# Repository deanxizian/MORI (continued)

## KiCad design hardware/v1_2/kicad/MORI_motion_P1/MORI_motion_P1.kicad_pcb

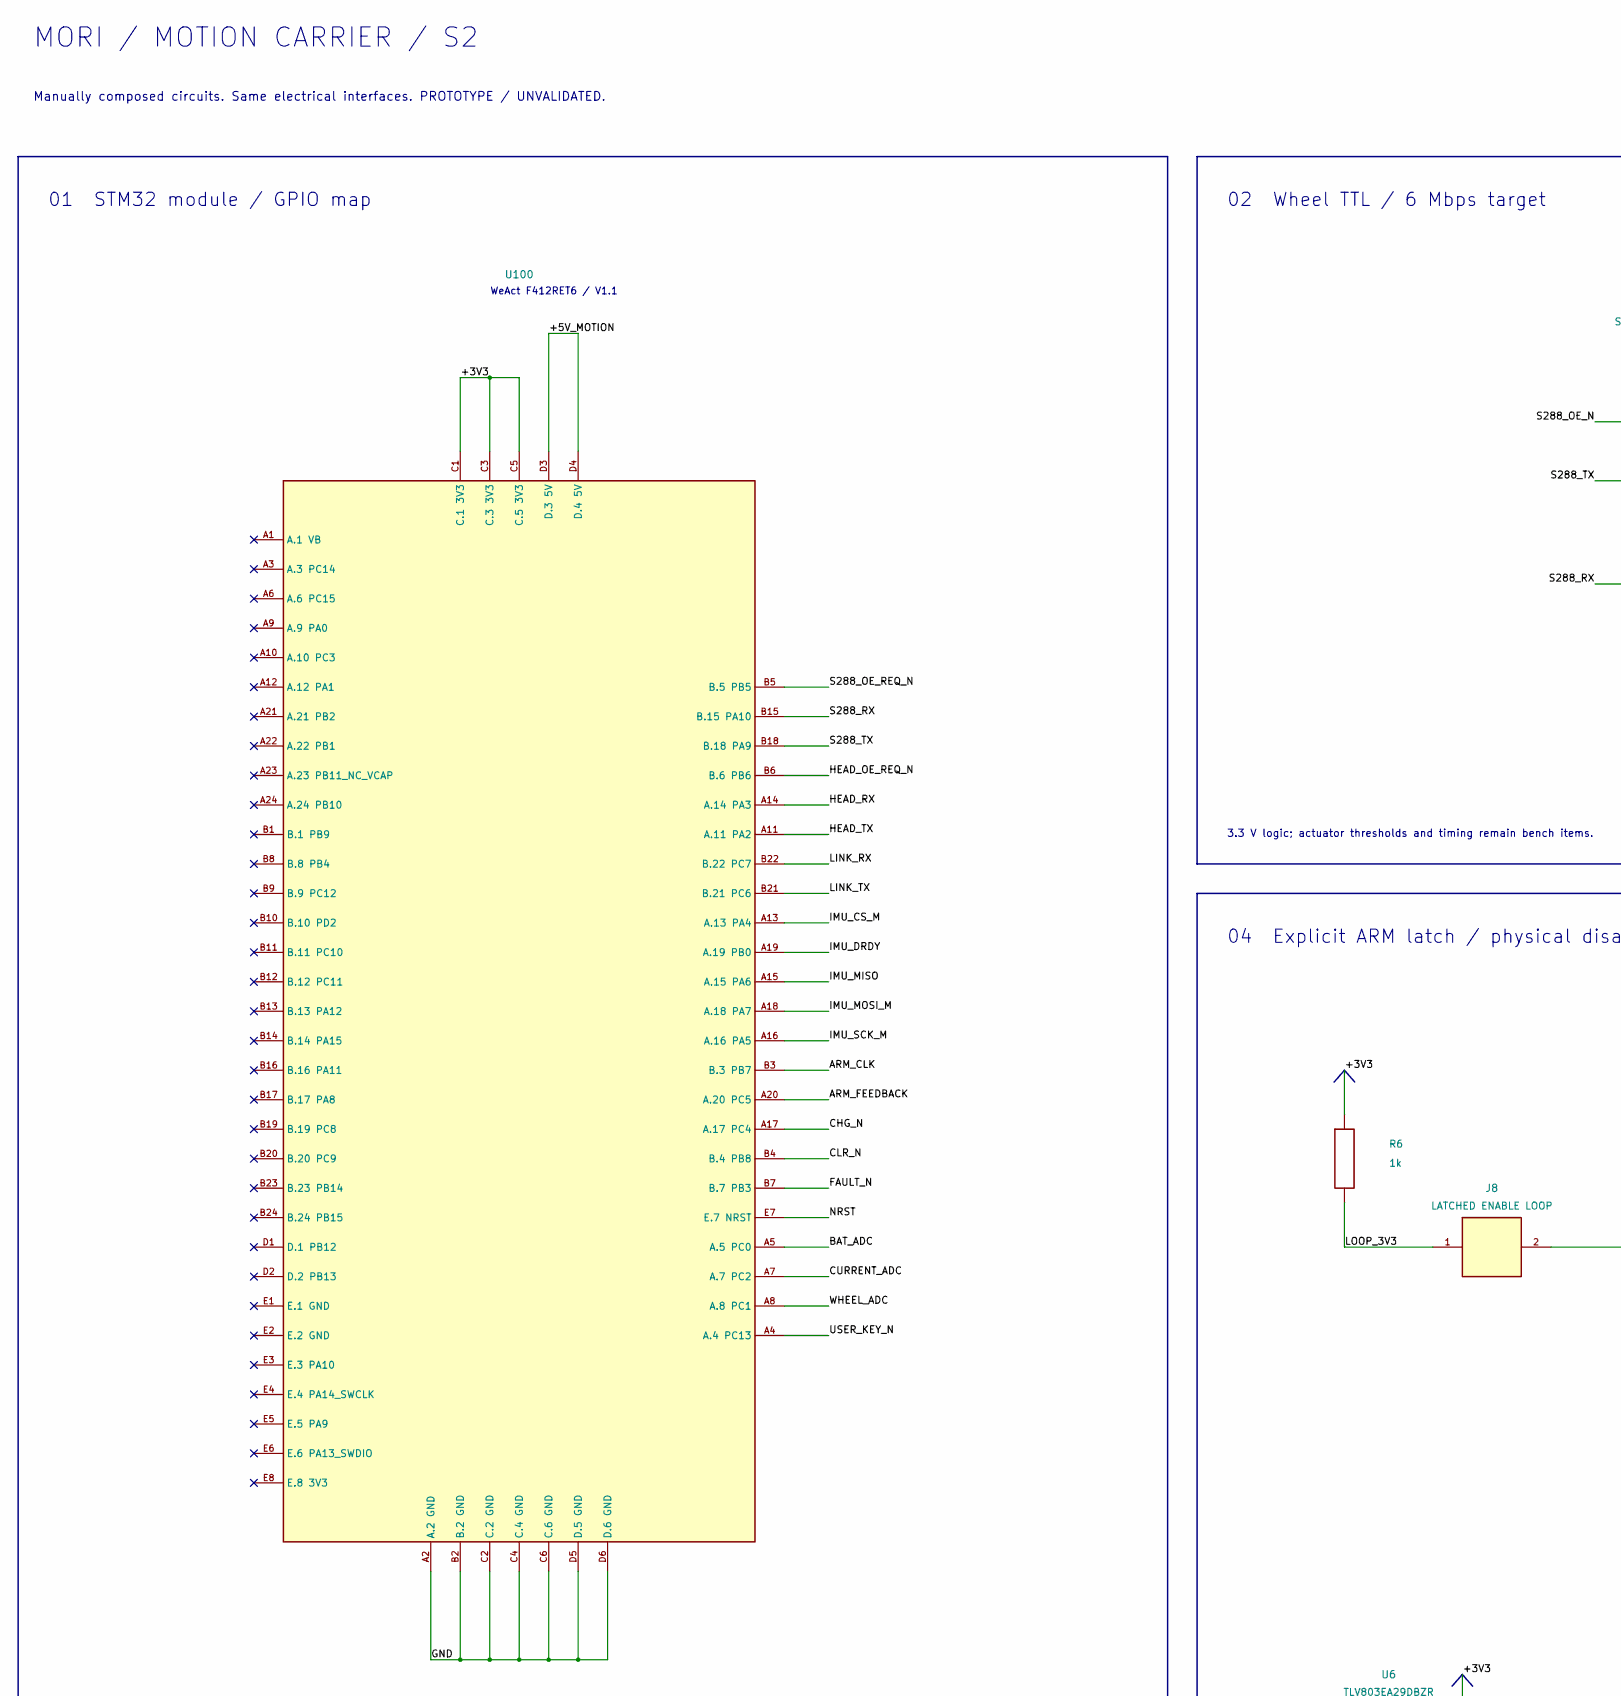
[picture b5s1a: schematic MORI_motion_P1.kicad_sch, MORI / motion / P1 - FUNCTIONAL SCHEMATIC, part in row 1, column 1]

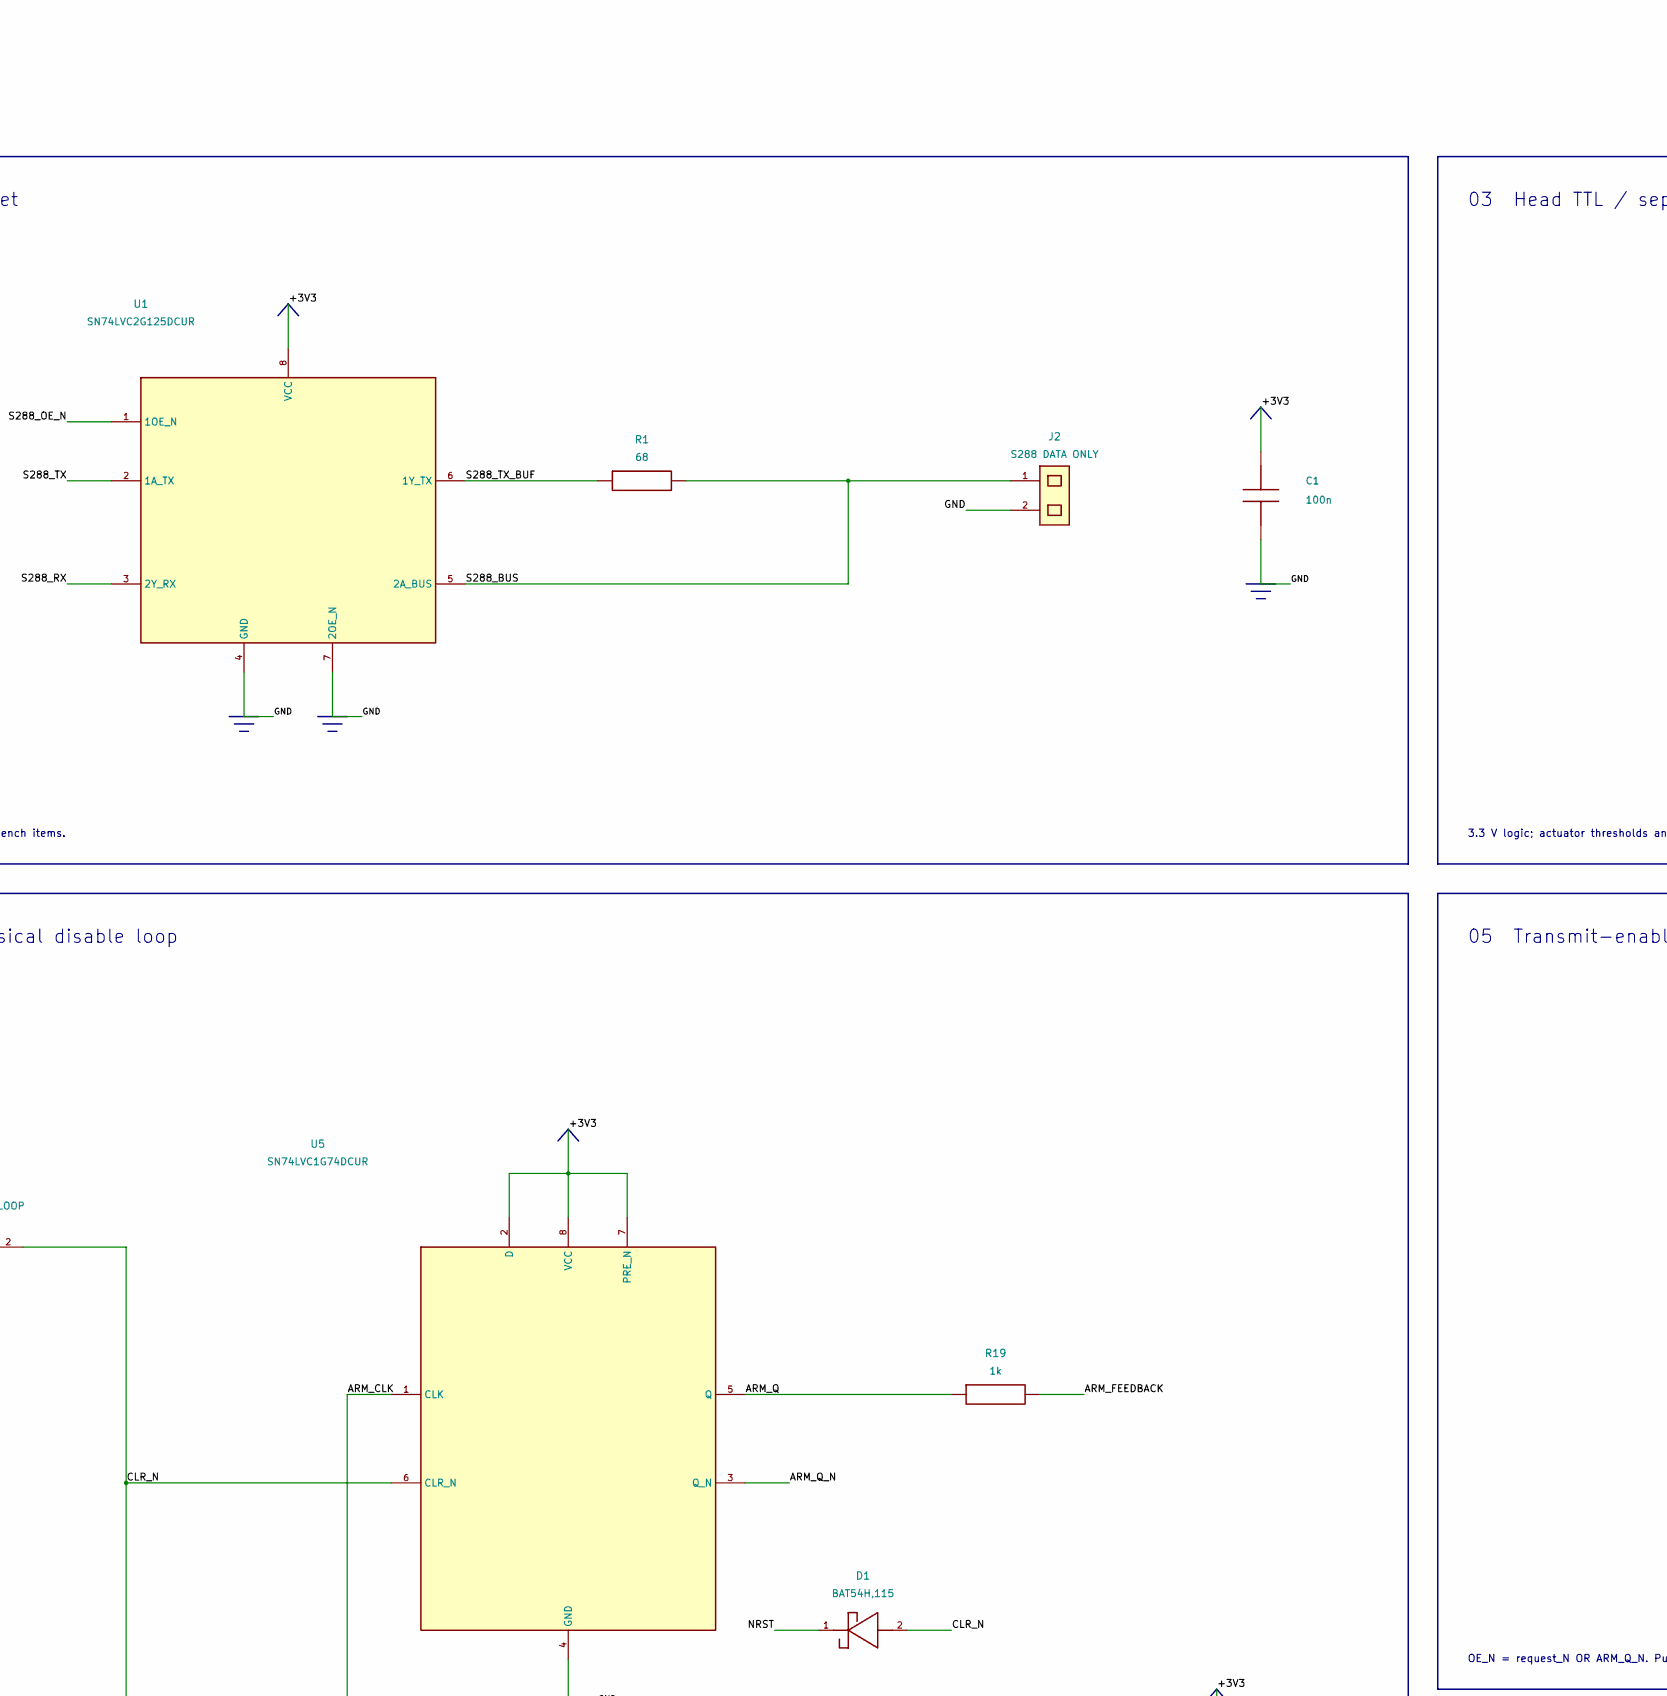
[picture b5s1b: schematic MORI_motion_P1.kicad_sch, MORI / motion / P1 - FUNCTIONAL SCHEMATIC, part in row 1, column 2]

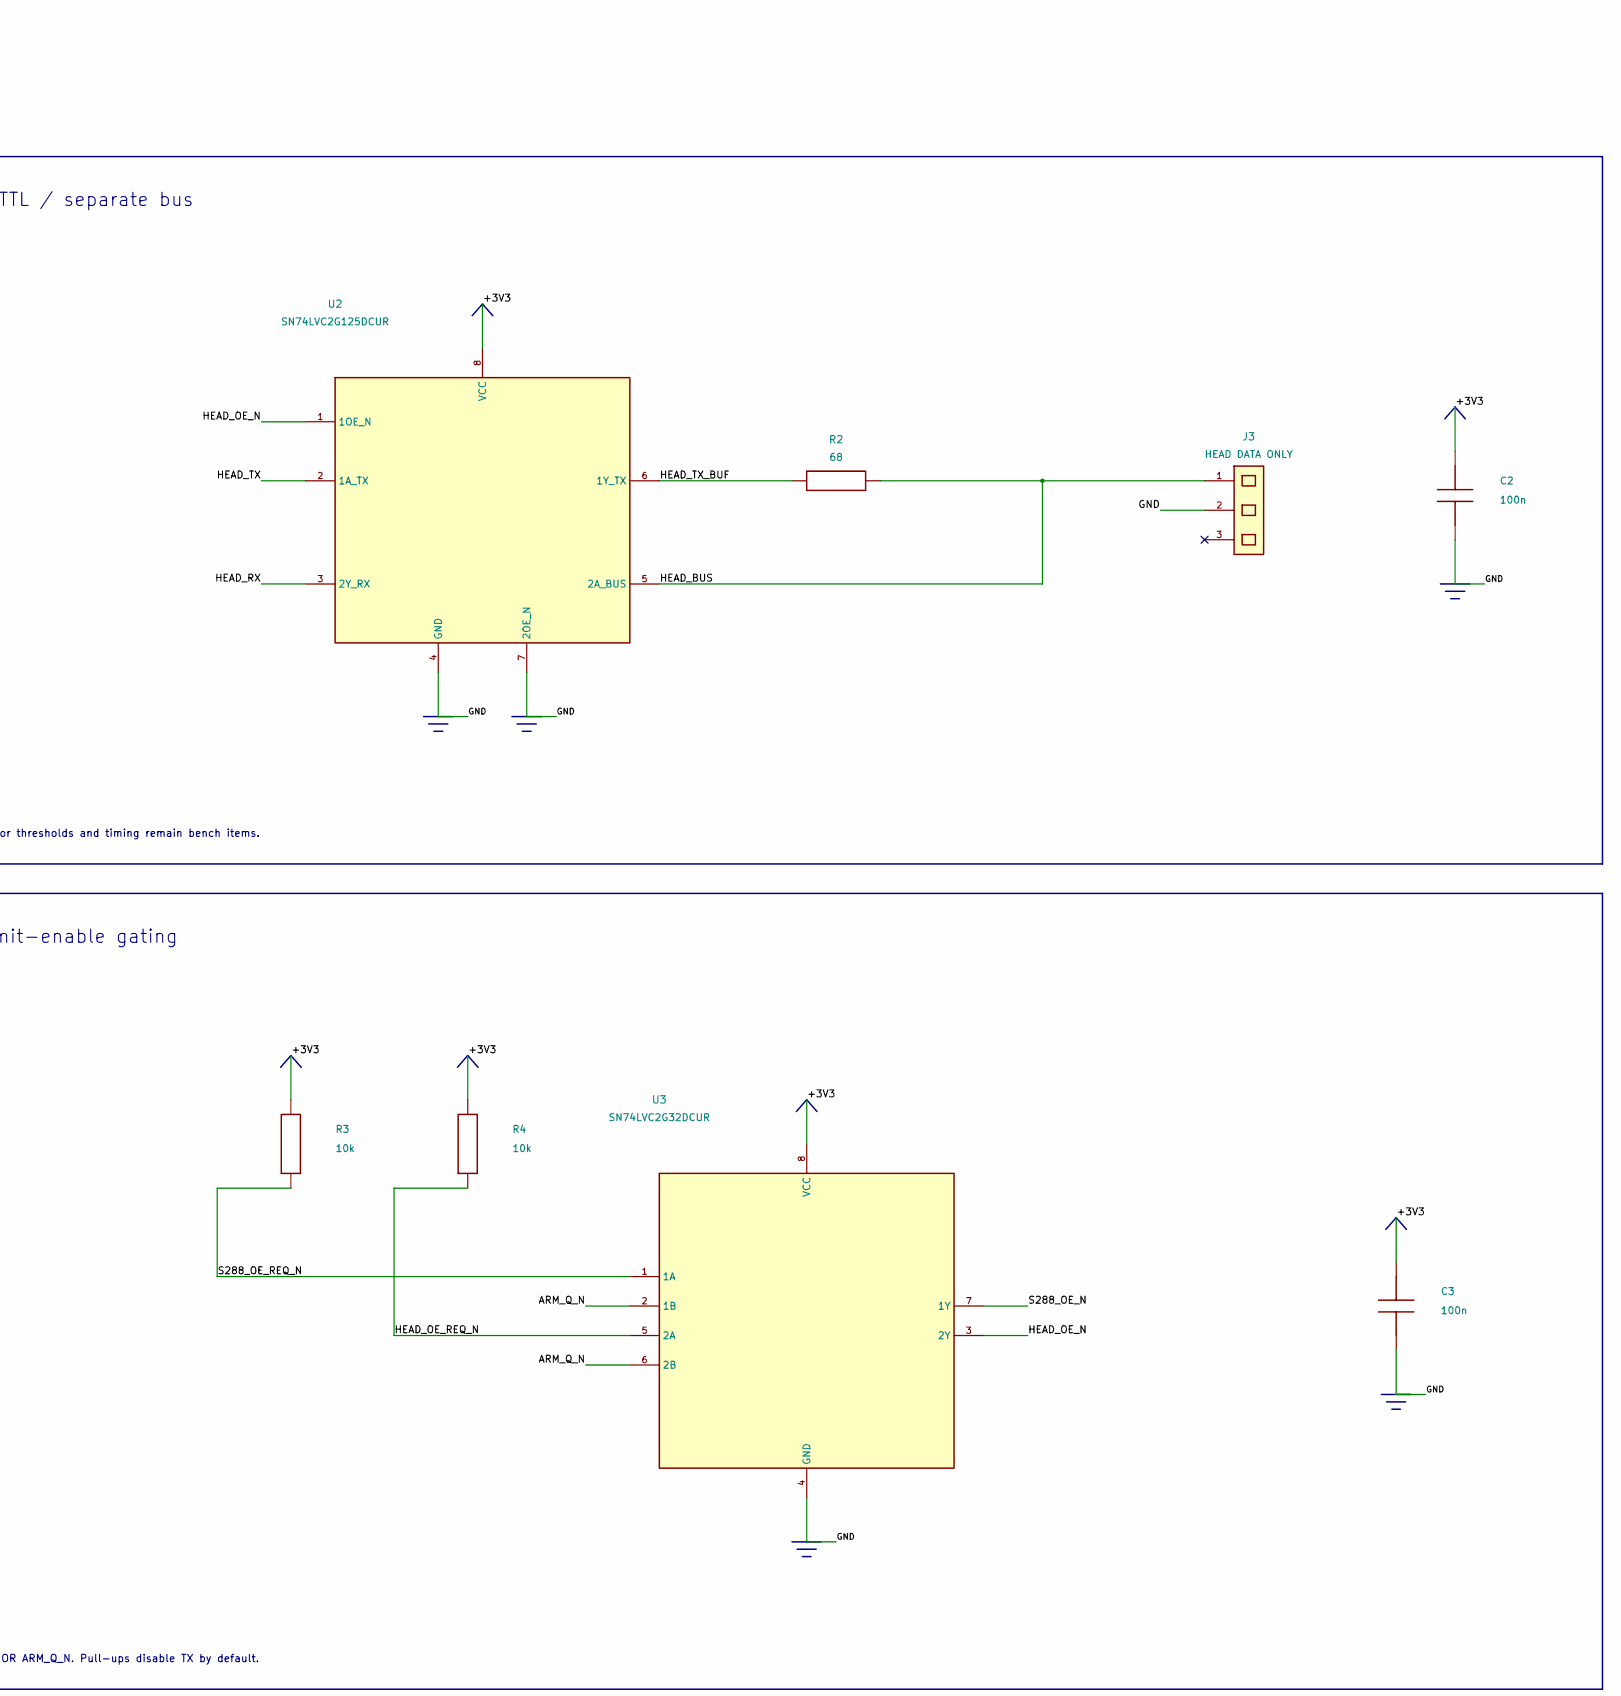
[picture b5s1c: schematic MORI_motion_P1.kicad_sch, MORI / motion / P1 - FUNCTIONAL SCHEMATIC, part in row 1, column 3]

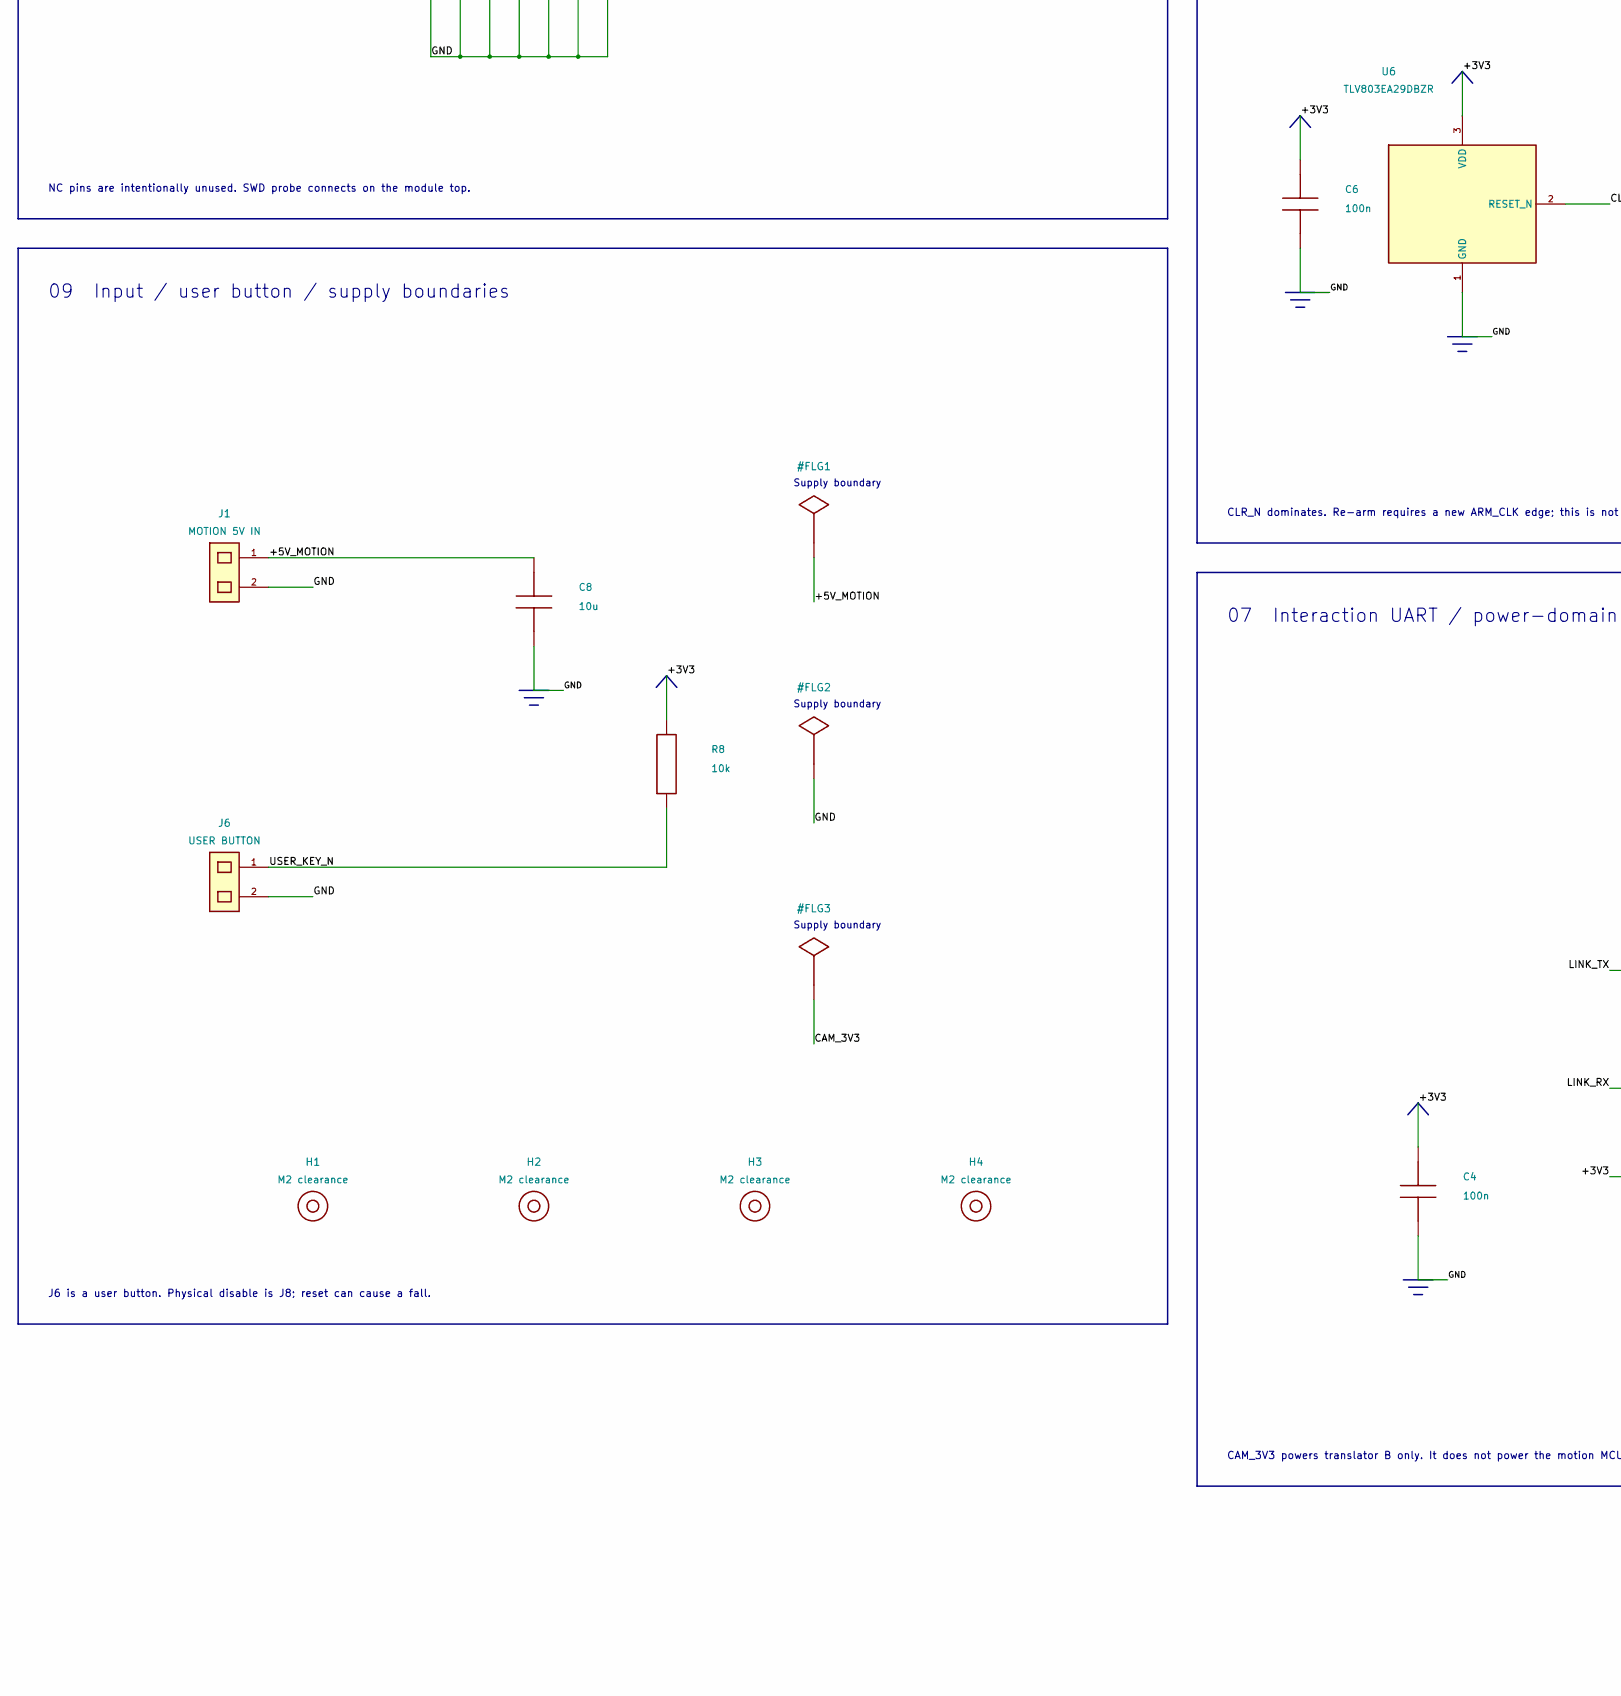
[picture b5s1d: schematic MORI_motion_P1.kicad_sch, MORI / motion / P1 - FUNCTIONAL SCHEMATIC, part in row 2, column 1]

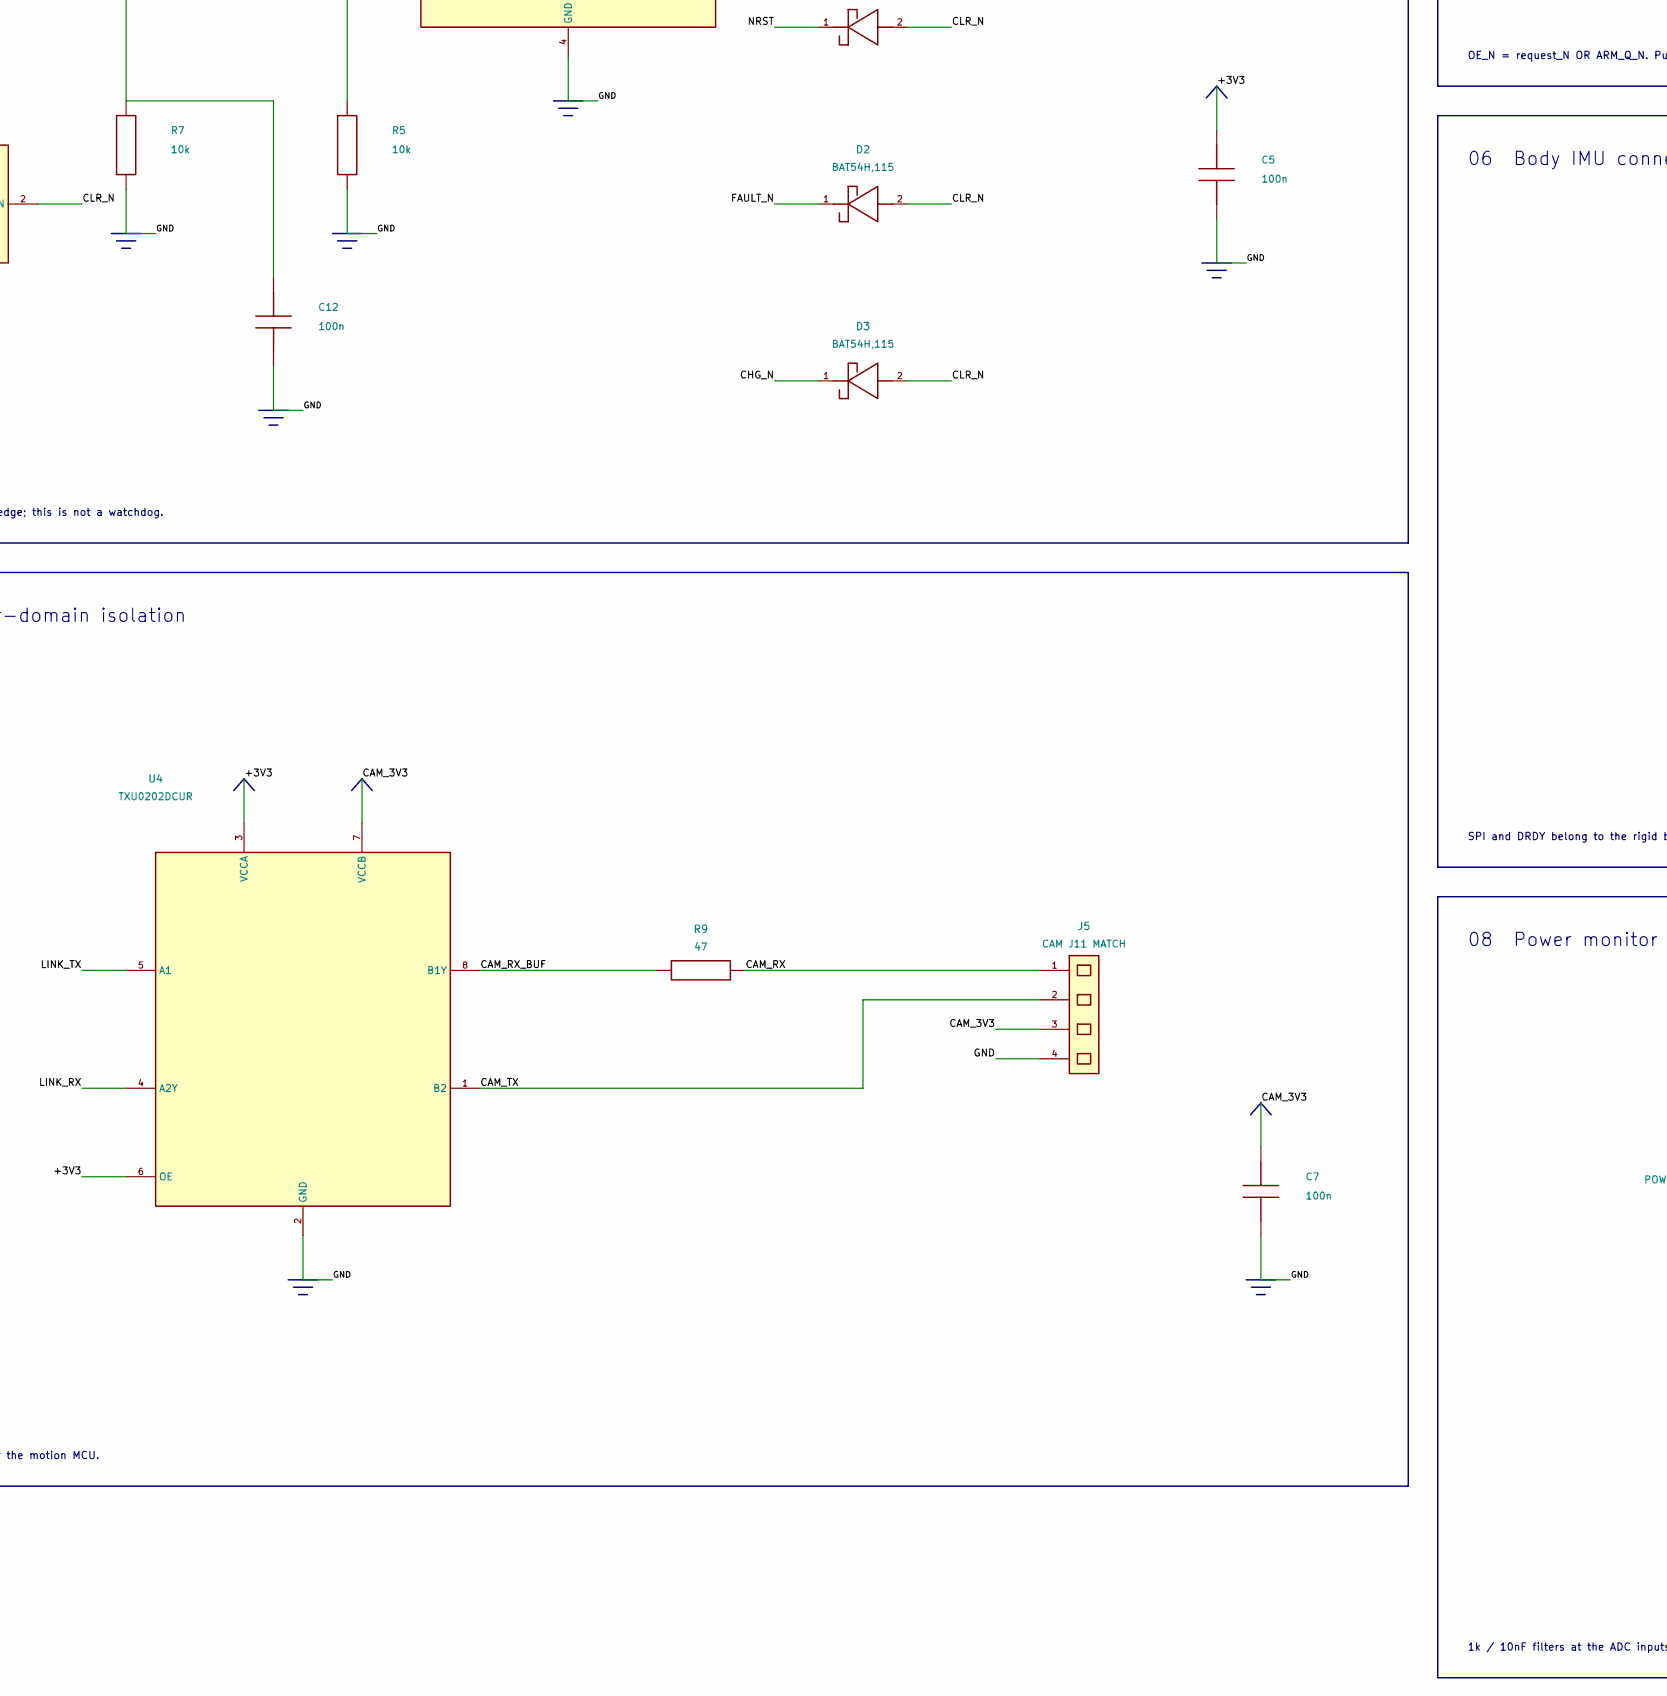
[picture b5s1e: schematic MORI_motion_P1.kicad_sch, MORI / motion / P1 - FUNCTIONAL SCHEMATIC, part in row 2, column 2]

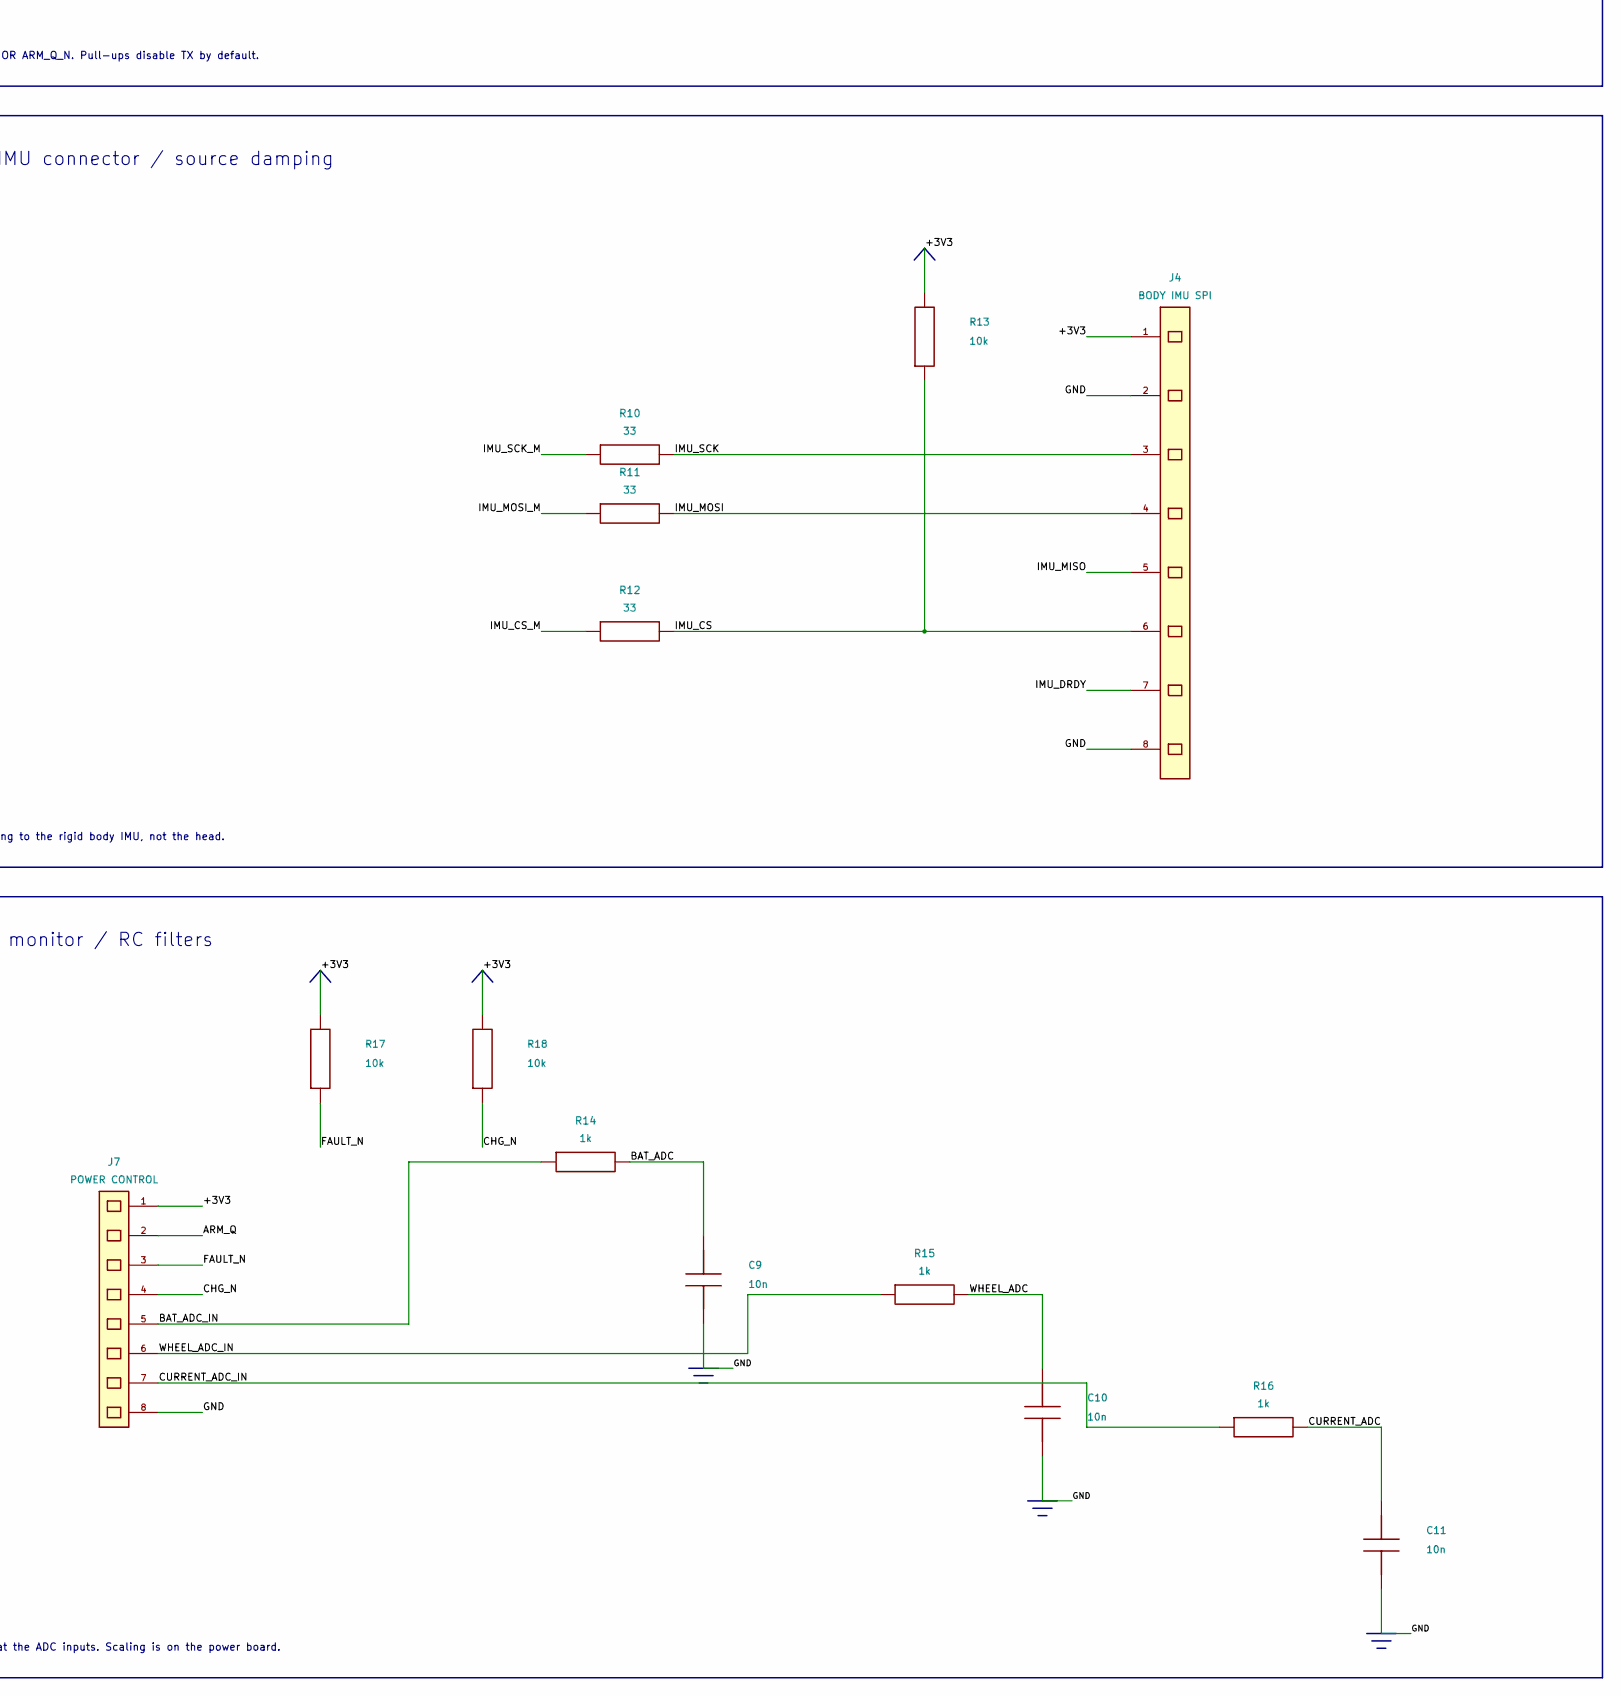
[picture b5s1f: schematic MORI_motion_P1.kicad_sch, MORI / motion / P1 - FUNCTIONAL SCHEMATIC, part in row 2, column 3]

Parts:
C1, C2, C3, C4, C5, C6, C7, C12: 100n; C_0603_1608Metric
C8: 10u; C_0603_1608Metric
C9, C10, C11: 10n; C_0603_1608Metric
D1, D2, D3: BAT54H,115; D_SOD-123
H1, H2, H3, H4: M2 clearance; MountingHole_2.2mm_M2
J1: MOTION 5V IN; JST_GH_BM02B-GHS-TBT_1x02-1MP_P1.25mm_Vertical
J2: S288 DATA ONLY; JST_GH_BM02B-GHS-TBT_1x02-1MP_P1.25mm_Vertical
J3: HEAD DATA ONLY; JST_GH_BM03B-GHS-TBT_1x03-1MP_P1.25mm_Vertical
J4: BODY IMU SPI; JST_GH_BM08B-GHS-TBT_1x08-1MP_P1.25mm_Vertical
J5: CAM J11 MATCH; JST_SH_BM04B-SRSS-TB_1x04-1MP_P1.00mm_Vertical
J6: USER BUTTON; JST_GH_BM02B-GHS-TBT_1x02-1MP_P1.25mm_Vertical
J7: POWER CONTROL; JST_GH_BM08B-GHS-TBT_1x08-1MP_P1.25mm_Vertical
J8: LATCHED ENABLE LOOP; JST_GH_BM02B-GHS-TBT_1x02-1MP_P1.25mm_Vertical
R1, R2: 68; R_0603_1608Metric
R3, R4, R5, R7, R8, R13, R17, R18: 10k; R_0603_1608Metric
R6, R14, R15, R16, R19: 1k; R_0603_1608Metric
R9: 47; R_0603_1608Metric
R10, R11, R12: 33; R_0603_1608Metric
U1, U2: SN74LVC2G125DCUR; VSSOP-8_2.3x2mm_P0.5mm
U3: SN74LVC2G32DCUR; VSSOP-8_2.3x2mm_P0.5mm
U4: TXU0202DCUR; VSSOP-8_2.3x2mm_P0.5mm
U5: SN74LVC1G74DCUR; VSSOP-8_2.3x2mm_P0.5mm
U6: TLV803EA29DBZR; SOT-23
U100: WeAct STM32F412RET6 64Pin V1.1; WeAct_F4_64Pin_V11

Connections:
/+3V3: C1.1, C2.1, C3.1, C4.1, C5.1, C6.1, J4.1, J7.1, R3.2, R4.2, R6.1, R8.2, R13.2, R17.2, R18.2, U1.8 (VCC), U2.8 (VCC), U3.8 (VCC), U4.3 (VCCA), U4.6 (OE), U5.2 (D), U5.7 (PRE_N), U5.8 (VCC), U6.3 (VDD), U100.C1 (C.1 3V3), U100.C3 (C.3 3V3), U100.C5 (C.5 3V3)
/+5V_MOTION: C8.1, J1.1, U100.D3 (D.3 5V), U100.D4 (D.4 5V)
/ARM_CLK: R5.1, U5.1 (CLK), U100.B3 (B.3 PB7)
/ARM_FEEDBACK: R19.2, U100.A20 (A.20 PC5)
/ARM_Q: J7.2, R19.1, U5.5 (Q)
/ARM_Q_N: U3.2 (1B), U3.6 (2B), U5.3 (Q_N)
/BAT_ADC: C9.1, R14.2, U100.A5 (A.5 PC0)
/BAT_ADC_IN: J7.5, R14.1
/CAM_3V3: C7.1, J5.3, U4.7 (VCCB)
/CAM_RX: J5.1, R9.2
/CAM_RX_BUF: R9.1, U4.8 (B1Y)
/CAM_TX: J5.2, U4.1 (B2)
/CHG_N: D3.1, J7.4, R18.1, U100.A17 (A.17 PC4)
/CLR_N: C12.1, D1.2, D2.2, D3.2, J8.2, R7.1, U5.6 (CLR_N), U6.2 (RESET_N), U100.B4 (B.4 PB8)
/CURRENT_ADC: C11.1, R16.2, U100.A7 (A.7 PC2)
/CURRENT_ADC_IN: J7.7, R16.1
/FAULT_N: D2.1, J7.3, R17.1, U100.B7 (B.7 PB3)
/GND: C1.2, C2.2, C3.2, C4.2, C5.2, C6.2, C7.2, C8.2, C9.2, C10.2, C11.2, C12.2, J1.2, J2.2, J3.2, J4.2, J4.8, J5.4, J6.2, J7.8, R5.2, R7.2, U1.4 (GND), U1.7 (2OE_N), U2.4 (GND), U2.7 (2OE_N), U3.4 (GND), U4.2 (GND), U5.4 (GND), U6.1 (GND), U100.A2 (A.2 GND), U100.B2 (B.2 GND), U100.C2 (C.2 GND), U100.C4 (C.4 GND), U100.C6 (C.6 GND), U100.D5 (D.5 GND), U100.D6 (D.6 GND)
/HEAD_BUS: J3.1, R2.2, U2.5 (2A_BUS)
/HEAD_OE_N: U2.1 (1OE_N), U3.3 (2Y)
/HEAD_OE_REQ_N: R4.1, U3.5 (2A), U100.B6 (B.6 PB6)
/HEAD_RX: U2.3 (2Y_RX), U100.A14 (A.14 PA3)
/HEAD_TX: U2.2 (1A_TX), U100.A11 (A.11 PA2)
/HEAD_TX_BUF: R2.1, U2.6 (1Y_TX)
/IMU_CS: J4.6, R12.2, R13.1
/IMU_CS_M: R12.1, U100.A13 (A.13 PA4)
/IMU_DRDY: J4.7, U100.A19 (A.19 PB0)
/IMU_MISO: J4.5, U100.A15 (A.15 PA6)
/IMU_MOSI: J4.4, R11.2
/IMU_MOSI_M: R11.1, U100.A18 (A.18 PA7)
/IMU_SCK: J4.3, R10.2
/IMU_SCK_M: R10.1, U100.A16 (A.16 PA5)
/LINK_RX: U4.4 (A2Y), U100.B22 (B.22 PC7)
/LINK_TX: U4.5 (A1), U100.B21 (B.21 PC6)
/LOOP_3V3: J8.1, R6.2
/NRST: D1.1, U100.E7 (E.7 NRST)
/S288_BUS: J2.1, R1.2, U1.5 (2A_BUS)
/S288_OE_N: U1.1 (1OE_N), U3.7 (1Y)
/S288_OE_REQ_N: R3.1, U3.1 (1A), U100.B5 (B.5 PB5)
/S288_RX: U1.3 (2Y_RX), U100.B15 (B.15 PA10)
/S288_TX: U1.2 (1A_TX), U100.B18 (B.18 PA9)
/S288_TX_BUF: R1.1, U1.6 (1Y_TX)
/USER_KEY_N: J6.1, R8.1, U100.A4 (A.4 PC13)
/WHEEL_ADC: C10.1, R15.2, U100.A8 (A.8 PC1)
/WHEEL_ADC_IN: J7.6, R15.1

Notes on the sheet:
MORI / MOTION CARRIER / S2
Manually composed circuits. Same electrical interfaces. PROTOTYPE / UNVALIDATED.
01 STM32 module / GPIO map
NC pins are intentionally unused. SWD probe connects on the module top.
WeAct F412RET6 / V1.1
02 Wheel TTL / 6 Mbps target
3.3 V logic; actuator thresholds and timing remain bench items.
03 Head TTL / separate bus
04 Explicit ARM latch / physical disable loop
CLR_N dominates. Re-arm requires a new ARM_CLK edge; this is not a watchdog.
05 Transmit-enable gating
OE_N = request_N OR ARM_Q_N. Pull-ups disable TX by default.
06 Body IMU connector / source damping
SPI and DRDY belong to the rigid body IMU, not the head.
07 Interaction UART / power-domain isolation
CAM_3V3 powers translator B only. It does not power the motion MCU.
08 Power monitor / RC filters
1k / 10nF filters at the ADC inputs. Scaling is on the power board.
09 Input / user button / supply boundaries
J6 is a user button. Physical disable is J8; reset can cause a fall.
Supply boundary
